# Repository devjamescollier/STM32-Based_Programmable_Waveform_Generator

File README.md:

# STM32-Based Programmable Waveform Generator

USB-powered programmable function generator built around an STM32C031K6T6 microcontroller and MCP4901 DAC. Generates clean sine, triangle, and square waveforms with amplitude control via potentiometer, mode selection via buttons, and visual feedback through status/signal LEDs.

Designed for lab and bench use with an SWD programming header, multiple test points, and robust power protection.

## Table of Contents
- [Schematic](#schematic)
- [Layout](#layout)
- [3D Model](#3d-model)
- [Overview](#overview)
- [Specifications](#specifications)
- [Results](#results)
- [Software](#software)
- [Tech Stack](#tech-stack)
- [Equipment](#equipment)
- [Manufacturing](#manufacturing)
- [Repository Structure](#repository-structure)
- [Contact](#contact)
- [License](#license)

## Schematic

## Layout

## 3D Model

## Overview

The board is a compact USB-powered waveform generator centred on an STM32C031K6T6 microcontroller.

| Section                         | Description                                                                                                            |
| ---                             | ---                                                                                                                    |
| **Digital Core**                | The STM32 generates waveform data and drives an MCP4901 8-bit SPI DAC.                                                 |
| **Analog Front-End**            | A TLV2372 dual op-amp and discrete MOSFET switching produce clean sine, triangle, and square outputs.                  |
| **User Interface**              | Three tactile switches provide waveform selection, mode/settings control, and reset. Five status/signal LEDs provide visual feedback, while a potentiometer controls amplitude. |
| **Power**                       | A USB Micro-B input supplies the board through an LM1117 3.3 V regulator with polyfuse protection.                     |

## Specifications

| Parameter                         | Value                                  |
| --------------------------------- | -------------------------------------- |
| **Microcontroller**               | STM32C031K6T6                          |
| **DAC**                           | MCP4901, 8-bit SPI                     |
| **Waveforms**                     | Sine, triangle, and square             |
| **Sine/Triangle Frequency Range** | 1 Hz–50 kHz                            |
| **Square-Wave Frequency Range**   | 1 Hz–100 kHz                           |
| **Amplitude**                     | 0–3.0 Vpp, controlled by potentiometer |
| **Output Impedance**              | ~50 Ω                                  |
| **Power Input**                   | 5 V USB                                |
| **Typical Current**               | 28 mA                                  |
| **Maximum Current**               | 45 mA                                  |
| **Regulation**                    | 3.3 V ± 1.5%                           |
| **Board size**                    | 52 mm × 48 mm                          |

## Results

PCB measurements from the hand-soldered prototype:

| Waveform     | Frequency | Amplitude | THD / Rise-Fall | Notes                           |
| -----------: | --------: | --------: | --------------: | ------------------------------: |
| **Sine**     | 1 kHz     | 2.98 Vpp  | 0.72% THD       | Clean across the full range     |
| **Triangle** | 1 kHz     | 2.95 Vpp  | —               | Linear slope confirmed          |
| **Square**   | 10 kHz    | 3.01 Vpp  | 12 ns / 14 ns   | Fast edges with minimal ringing |

Frequency response, amplitude accuracy (±1.2%), and load regulation were verified using an Agilent Technologies InfiniiVision MSO-X 3034A and Digilent Analog Discovery 3.

## Software

The firmware targets the STM32C031K6T6 and is written in C.

### Programming

1. Create a new STM32CubeIDE project targeting the STM32C031K6T6.
2. Replace the generated `Core/Src/main.c` with [`Software/main.c`](Software/main.c).
3. Configure the required GPIO, SPI, ADC, and timer peripherals.
4. Connect an ST-Link/V2 to the SWD header.
5. Build and flash the firmware through SWD.

## Tech Stack

| PCB Design | Firmware Development | Version Control | Repository Hosting | Circuit Simulation | IDE         | Language |
| :--------: | :------------------: | :-------------: | :----------------: | :----------------: | :---------: | :------: |
|  |  |  |  |  |  |  |

## Equipment

| Tool                   | Model                                          | Purpose |
| ---------------------- | ---------------------------------------------- | ------- |
| **Oscilloscope**       | Agilent Technologies InfiniiVision MSO-X 3034A | Waveform capture, THD, and rise/fall-time measurements |
| **Mixed-signal tool**  | Digilent Analog Discovery 3                    | Frequency-response and spectrum analysis               |
| **Multimeter**         | Tektronix DMM4020A                             | DC accuracy and current-draw measurements              |
| **Programmer**         | ST-Link/V2                                     | Firmware flashing and SWD debugging                    |
| **USB Power Analyzer** | —                                              | Input-current and efficiency verification              |
| **Soldering station**  | —                                              | Hand assembly of all SMD and through-hole components   |

## Manufacturing

Production files are provided in the [`Manufacturing`](Manufacturing/) directory:

| File | Purpose |
| ---- | ------- |
| [`JLCPCB/Waveform_Generator_Gerbers.zip`](Manufacturing/JLCPCB/Waveform_Generator_Gerbers.zip) | Gerber and drill archive, ready to upload to JLCPCB |
| [`JLCPCB/Waveform_Generator_JLCPCB_BOM.csv`](Manufacturing/JLCPCB/Waveform_Generator_JLCPCB_BOM.csv) | Bill of materials with LCSC part numbers (JLCPCB format) |
| [`JLCPCB/Waveform_Generator_JLCPCB_CPL.csv`](Manufacturing/JLCPCB/Waveform_Generator_JLCPCB_CPL.csv) | Component placement list (JLCPCB format) |
| [`Gerbers`](Manufacturing/Gerbers/) | Individual Gerber (copper, mask, silkscreen, paste, outline) and Excellon drill files |
| [`Assembly/STM32-Based_Programmable_Waveform_Generator-all-pos.csv`](Manufacturing/Assembly/STM32-Based_Programmable_Waveform_Generator-all-pos.csv) | KiCad component position file (generic pick-and-place) |

### Ordering from JLCPCB

1. Upload `Waveform_Generator_Gerbers.zip` (2-layer, 52 mm × 48 mm).
2. Enable PCB Assembly, then upload `Waveform_Generator_JLCPCB_BOM.csv` and `Waveform_Generator_JLCPCB_CPL.csv`.
3. Check component rotation and polarity in the JLCPCB placement preview, especially U1, U2, U4, U5, Q3, Q4, D1–D5, and the tantalum capacitors C7 and C8.

> **Note:** At the time of writing, U1 (STM32C031K6T6, LCSC C5456169) and J2 (Amphenol 10104110-0001LF, LCSC C2931352) are stocked by LCSC but not held in JLCPCB's assembly inventory. Pre-order them into your JLCPCB parts library before placing the assembly order. TP1–TP4 are bare test pads and are not assembled.

Verify all fabrication outputs against the KiCad design before ordering.

## Repository Structure

```text
STM32-Based_Programmable_Waveform_Generator
├── .gitignore                                                                  Git ignore rules for KiCad and OS temporary files
├── Docs                                                                        Documentation
│   └── Images                                                                  Board render, layout, and schematic images
│       ├── STM32-Based_Programmable_Waveform_Generator_3D_Model.png            3D render of the board
│       ├── STM32-Based_Programmable_Waveform_Generator_Schematic_Layout.png    PCB layout
│       ├── STM32-Based_Programmable_Waveform_Generator_Schematic.png           Schematic (PNG)
│       └── STM32-Based_Programmable_Waveform_Generator_Schematic.pdf           Schematic (PDF)
├── Hardware                                                                    Hardware design files
│   └── KiCad_Files                                                             KiCad project, schematic, PCB, and project libraries
│       ├── 3D_Models                                                           STEP models used in the 3D render
│       │   ├── LM1117IMP-3-3-NOPB.stp                                          LM1117IMP-3.3/NOPB linear voltage regulator
│       │   ├── TC33X-2-XXX.stp                                                 Bourns TC33X-2-103E potentiometer
│       │   └── USB-B-Micro.stp                                                 USB Micro-B receptacle
│       ├── Footprints                                                          Project footprint library
│       │   └── LM1117.pretty                                                   LM1117 footprints
│       │       ├── DCY0004A_L.kicad_mod
│       │       ├── DCY0004A_M.kicad_mod
│       │       └── DCY0004A_N.kicad_mod
│       ├── Symbols                                                             Project symbol library
│       │   └── LM1117
│       │       └── LM1117.kicad_sym                                            LM1117 linear voltage regulator symbol
│       ├── STM32-Based_Programmable_Waveform_Generator.kicad_pcb               KiCad PCB file
│       ├── STM32-Based_Programmable_Waveform_Generator.kicad_pro               KiCad project file
│       ├── STM32-Based_Programmable_Waveform_Generator.kicad_sch               KiCad schematic file
│       └── sym-lib-table                                                       Project symbol library table
├── Manufacturing                                                               Fabrication and assembly outputs
│   ├── Assembly                                                                Generic assembly data
│   │   └── STM32-Based_Programmable_Waveform_Generator-all-pos.csv             KiCad component position file
│   ├── Gerbers                                                                 Individual Gerber and drill files
│   │   ├── STM32-Based_Programmable_Waveform_Generator-B_Cu.gbl                Bottom copper
│   │   ├── STM32-Based_Programmable_Waveform_Generator-B_Mask.gbs              Bottom solder mask
│   │   ├── STM32-Based_Programmable_Waveform_Generator-B_Paste.gbp             Bottom paste
│   │   ├── STM32-Based_Programmable_Waveform_Generator-B_Silkscreen.gbo        Bottom silkscreen
│   │   ├── STM32-Based_Programmable_Waveform_Generator-Edge_Cuts.gm1           Board outline
│   │   ├── STM32-Based_Programmable_Waveform_Generator-F_Cu.gtl                Top copper
│   │   ├── STM32-Based_Programmable_Waveform_Generator-F_Mask.gts              Top solder mask
│   │   ├── STM32-Based_Programmable_Waveform_Generator-F_Paste.gtp             Top paste
│   │   ├── STM32-Based_Programmable_Waveform_Generator-F_Silkscreen.gto        Top silkscreen
│   │   ├── STM32-Based_Programmable_Waveform_Generator-NPTH.drl                Non-plated drill file
│   │   └── STM32-Based_Programmable_Waveform_Generator-PTH.drl                 Plated drill file
│   └── JLCPCB                                                                  Files ready to upload to JLCPCB
│       ├── Waveform_Generator_Gerbers.zip                                      Gerber and drill archive
│       ├── Waveform_Generator_JLCPCB_BOM.csv                                   Bill of materials with LCSC part numbers
│       └── Waveform_Generator_JLCPCB_CPL.csv                                   Component placement list
├── Software                                                                    Firmware
│   ├── LICENSE                                                                 MIT License for firmware
│   └── main.c                                                                  Firmware for the STM32C031K6T6
├── LICENSE                                                                     CERN Open Hardware Licence Version 2 – Permissive for hardware
└── README.md                                                                   Project README
```

## Contact
- GitHub: [@devjamescollier](https://github.com/devjamescollier)
- Email: [jwcollie@usc.edu](mailto:jwcollie@usc.edu)

## License

Copyright © 2026 James Collier

The hardware design files are licensed under the CERN Open Hardware
Licence Version 2 – Permissive. See [LICENSE](LICENSE).

The firmware is licensed under the MIT License. See
[Software/LICENSE](Software/LICENSE).

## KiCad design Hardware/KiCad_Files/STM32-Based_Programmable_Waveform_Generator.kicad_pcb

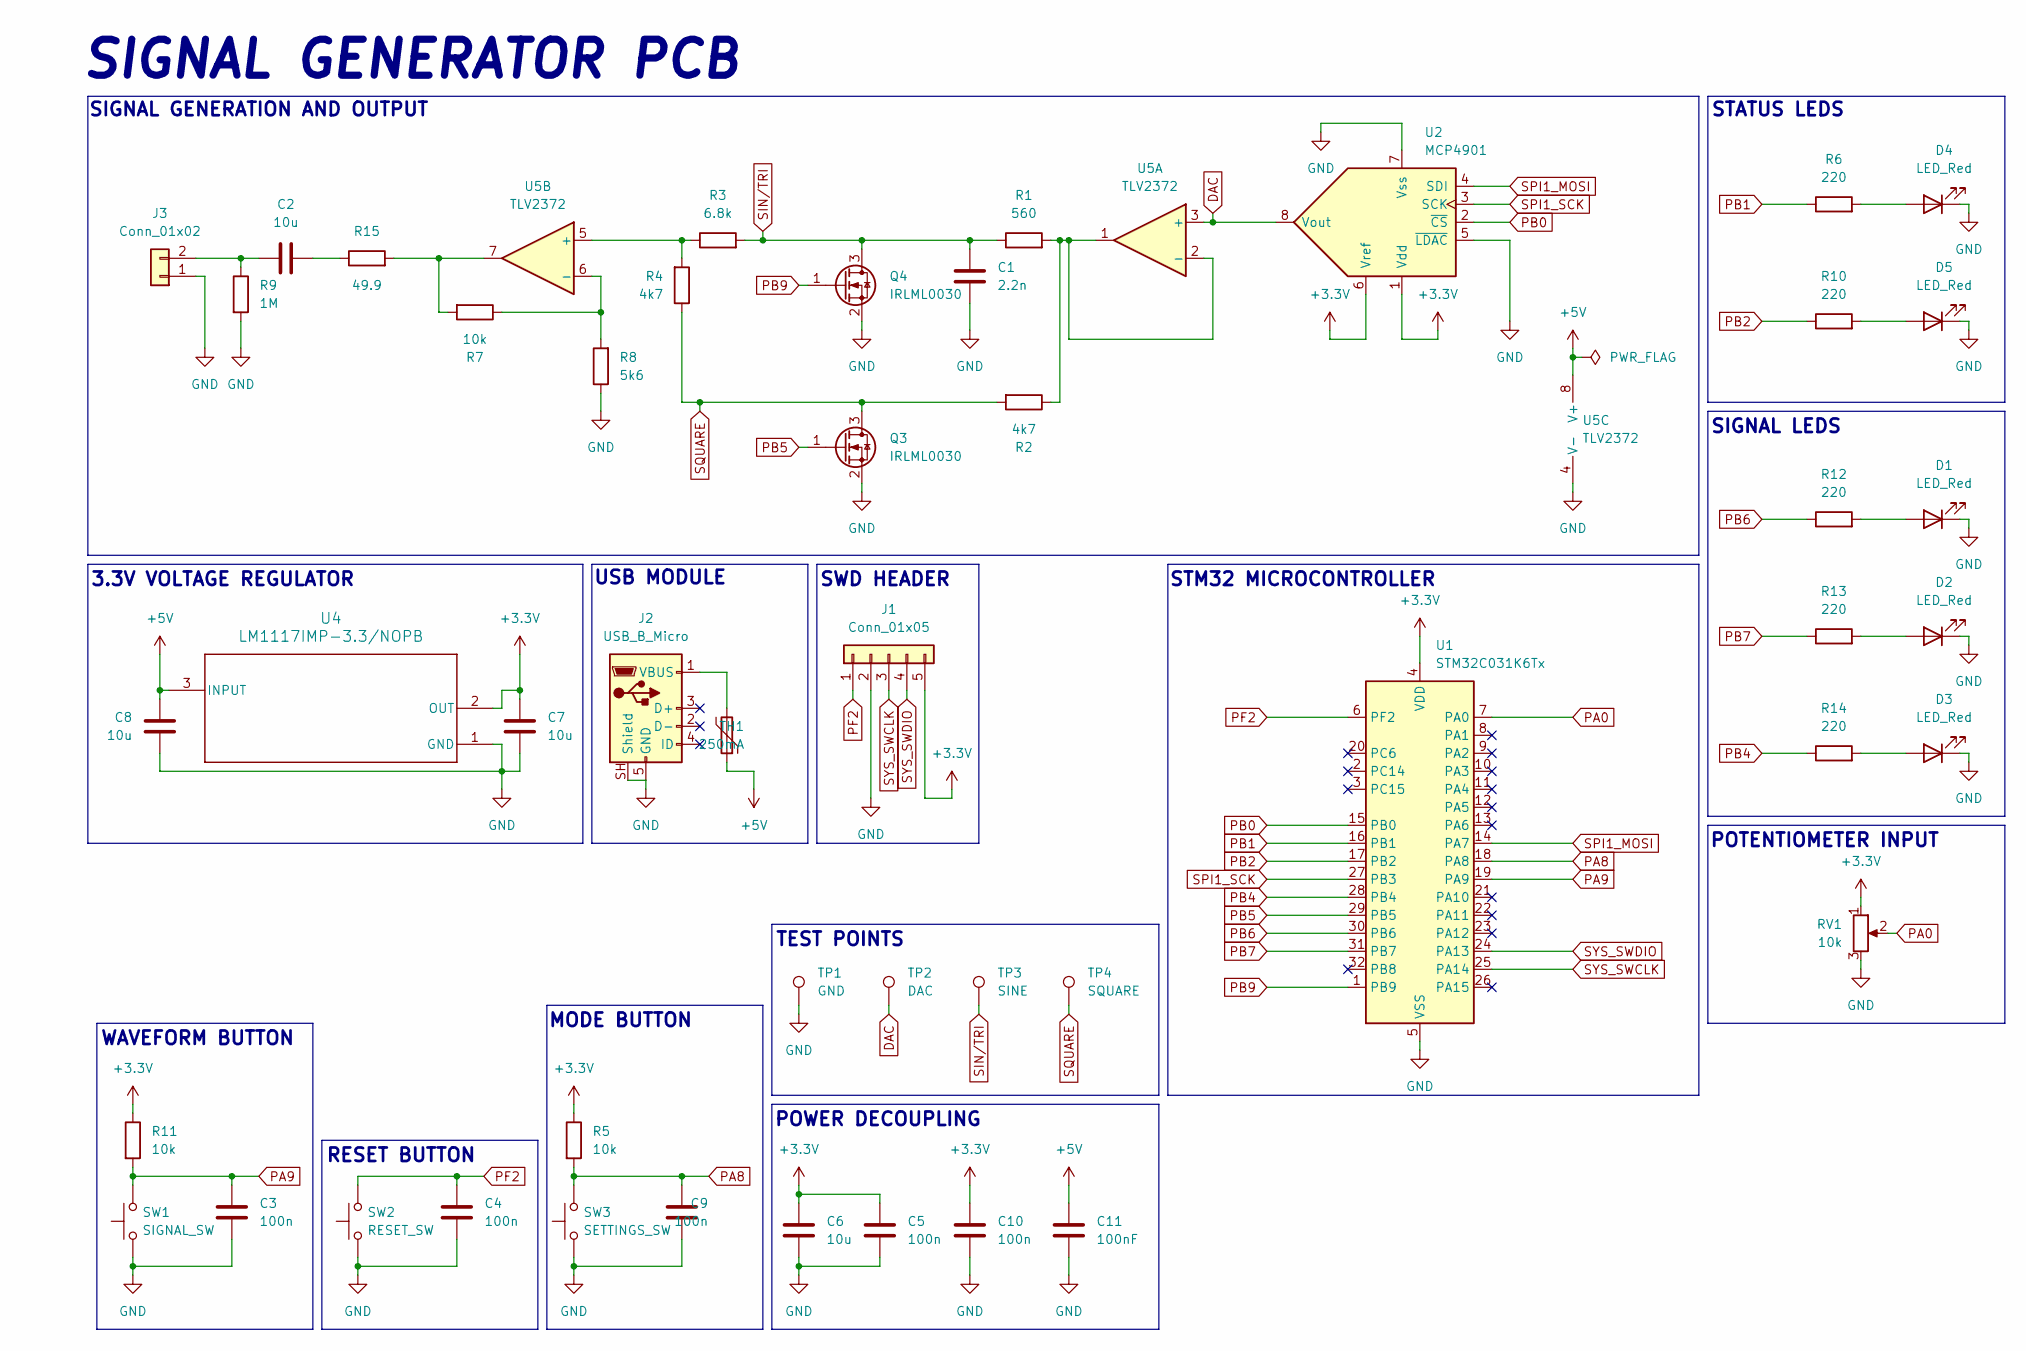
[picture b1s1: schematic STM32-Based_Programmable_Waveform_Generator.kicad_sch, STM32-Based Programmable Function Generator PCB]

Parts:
C1: 2.2n; C_0805_2012Metric
C2: 10u; C_1206_3216Metric
C3, C4, C5, C9, C10: 100n; C_0805_2012Metric
C6: 10u; C_0805_2012Metric
C7, C8: 10u; CP_EIA-3216-18_Kemet-A
C11: 100nF; C_0805_2012Metric
D1, D2, D3, D4, D5: LED_Red; LED_0805_2012Metric
J1: Conn_01x05; PinHeader_1x05_P2.54mm_Horizontal
J2: USB_B_Micro; USB_Micro-B_Amphenol_10104110_Horizontal
J3: Conn_01x02; JST_XH_B2B-XH-A_1x02_P2.50mm_Vertical
Q3, Q4: IRLML0030; SOT-23
R1: 560; R_0805_2012Metric
R2, R4: 4k7; R_0805_2012Metric
R3: 6.8k; R_0805_2012Metric
R5, R7, R11: 10k; R_0805_2012Metric
R6, R10, R12, R13, R14: 220; R_0805_2012Metric
R8: 5k6; R_0805_2012Metric
R9: 1M; R_0805_2012Metric
R15: 49.9; R_0805_2012Metric
RV1: 10k; Potentiometer_Bourns_TC33X_Vertical
SW1: SIGNAL_SW; SW_PUSH_6mm
SW2: RESET_SW; SW_PUSH_6mm
SW3: SETTINGS_SW; SW_PUSH_6mm
TH1: 250mA; Fuse_1206_3216Metric
TP1: GND; TestPoint_THTPad_D2.5mm_Drill1.2mm
TP2: DAC; TestPoint_THTPad_D2.5mm_Drill1.2mm
TP3: SINE; TestPoint_THTPad_D2.5mm_Drill1.2mm
TP4: SQUARE; TestPoint_THTPad_D2.5mm_Drill1.2mm
U1: STM32C031K6Tx; LQFP-32_7x7mm_P0.8mm
U2: MCP4901; SOIC-8_3.9x4.9mm_P1.27mm
U4: LM1117IMP-3.3/NOPB; SOT-223-3_TabPin2
U5: TLV2372; SOIC-8_3.9x4.9mm_P1.27mm

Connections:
+3.3V: C5.1, C6.1, C7.1, C10.1, J1.5, R5.1, R11.1, RV1.1, U1.4 (VDD), U2.1 (Vdd), U2.6 (Vref), U4.2 (OUT)
+5V: C8.1, C11.1, TH1.1, U4.3 (INPUT), U5.8 (V+)
DAC: TP2.1 (1_1), U2.8 (Vout), U5.3 (+)
GND: C1.2, C3.2, C4.2, C5.2, C6.2, C7.2, C8.2, C9.1, C10.2, C11.2, D1.1 (K), D2.1 (K), D3.1 (K), D4.1 (K), D5.1 (K), J1.2, J2.5 (GND), J2.SH (Shield), J3.1, Q3.2 (S), Q4.2 (S), R8.1, R9.2, RV1.3, SW1.1, SW2.1, SW3.1, TP1.1 (1_1), U1.5 (VSS), U2.5 (~LDAC), U2.7 (Vss), U4.1 (GND), U5.4 (V-)
unnamed: C2.2, R15.1
unnamed: D1.2 (A), R12.2
unnamed: D2.2 (A), R13.2
unnamed: D3.2 (A), R14.2
unnamed: D4.2 (A), R6.2
unnamed: D5.2 (A), R10.2
unnamed: J2.1 (VBUS), TH1.2
unnamed: C2.1, J3.2, R9.1
unnamed: R7.2, R15.2, U5.7
unnamed: R1.2, R2.1, U5.1, U5.2 (-)
unnamed: R3.1, R4.2, U5.5 (+)
unnamed: R7.1, R8.2, U5.6 (-)
PA0: RV1.2, U1.7 (PA0)
PA8: C9.2, R5.2, SW3.2, U1.18 (PA8)
PA9: C3.1, R11.2, SW1.2, U1.19 (PA9)
PB0: U1.15 (PB0), U2.2 (~CS)
PB1: R6.1, U1.16 (PB1)
PB2: R10.1, U1.17 (PB2)
PB4: R14.1, U1.28 (PB4)
PB5: Q3.1 (G), U1.29 (PB5)
PB6: R12.1, U1.30 (PB6)
PB7: R13.1, U1.31 (PB7)
PB9: Q4.1 (G), U1.1 (PB9)
PF2: C4.1, J1.1, SW2.2, U1.6 (PF2)
SIN/TRI: C1.1, Q4.3 (D), R1.1, R3.2, TP3.1 (1_1)
SPI1_MOSI: U1.14 (PA7), U2.4 (SDI)
SPI1_SCK: U1.27 (PB3), U2.3 (SCK)
SQUARE: Q3.3 (D), R2.2, R4.1, TP4.1 (1_1)
SYS_SWCLK: J1.3, U1.25 (PA14)
SYS_SWDIO: J1.4, U1.24 (PA13)

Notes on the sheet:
WAVEFORM BUTTON
POWER DECOUPLING
SIGNAL GENERATOR PCB
SWD HEADER
STATUS LEDS
SIGNAL LEDS
MODE BUTTON
RESET BUTTON
TEST POINTS
POTENTIOMETER INPUT
SIGNAL GENERATION AND OUTPUT
USB MODULE
STM32 MICROCONTROLLER
3.3V VOLTAGE REGULATOR

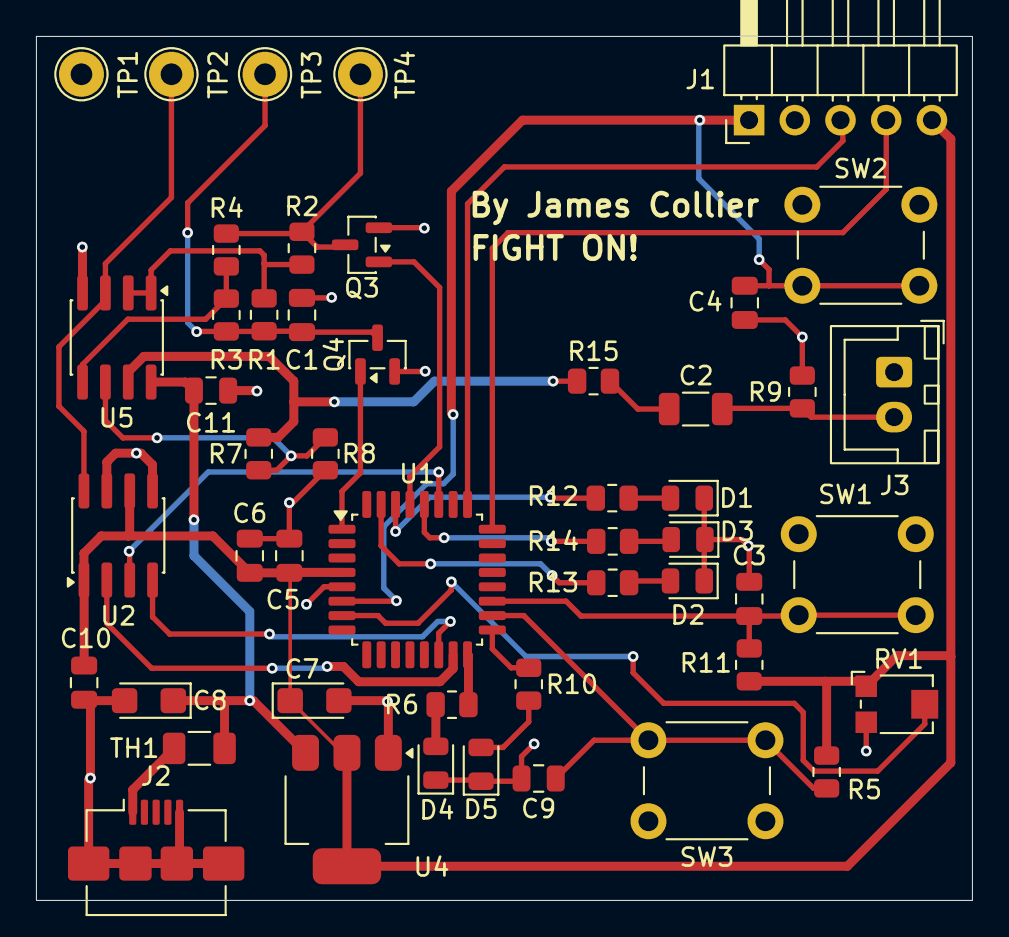
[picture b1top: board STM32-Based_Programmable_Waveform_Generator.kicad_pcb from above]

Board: 2 copper layers, 52.0 x 48.0 mm, 49 parts (0 on the bottom side), 34 nets.

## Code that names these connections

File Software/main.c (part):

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
static void OutputRouting_Update(void)
{
  const bool square = (waveform == WAVE_SQUARE);

  /* Q3/PB5 mutes the square path; Q4/PB9 mutes the sine/triangle path. */
  HAL_GPIO_WritePin(GPIOB, GPIO_PIN_5, square ? GPIO_PIN_RESET : GPIO_PIN_SET);
  HAL_GPIO_WritePin(GPIOB, GPIO_PIN_9, square ? GPIO_PIN_SET : GPIO_PIN_RESET);

  HAL_GPIO_WritePin(GPIOB, GPIO_PIN_6,
                    (waveform == WAVE_SINE) ? GPIO_PIN_SET : GPIO_PIN_RESET);
  HAL_GPIO_WritePin(GPIOB, GPIO_PIN_4,
                    (waveform == WAVE_TRIANGLE) ? GPIO_PIN_SET : GPIO_PIN_RESET);
  HAL_GPIO_WritePin(GPIOB, GPIO_PIN_7,
                    square ? GPIO_PIN_SET : GPIO_PIN_RESET);
}

static void ControlLeds_Update(void)
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  /*Configure GPIO pin Output Level */
  HAL_GPIO_WritePin(LD3_GPIO_Port, LD3_Pin, GPIO_PIN_RESET);

  /*Configure GPIO pins : PB9 PB0 PB1 PB2
                           PB4 PB5 PB6 PB7 */
  GPIO_InitStruct.Pin = GPIO_PIN_9|GPIO_PIN_0|GPIO_PIN_1|GPIO_PIN_2
                          |GPIO_PIN_4|GPIO_PIN_5|GPIO_PIN_6|GPIO_PIN_7;
  GPIO_InitStruct.Mode = GPIO_MODE_OUTPUT_PP;
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  GPIO_InitStruct.Pull = GPIO_NOPULL;
  HAL_GPIO_Init(T_NRST_GPIO_Port, &GPIO_InitStruct);

  /*Configure GPIO pins : PA8 PA9 */
  GPIO_InitStruct.Pin = GPIO_PIN_8|GPIO_PIN_9;
  GPIO_InitStruct.Mode = GPIO_MODE_IT_FALLING;
  GPIO_InitStruct.Pull = GPIO_PULLUP;
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
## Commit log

2026-05-26 Add project licenses
2026-05-27 Add KiCad symbols, footprints, and 3D models
2026-05-29 Add schematic and KiCad project file
2026-05-31 Add routed PCB layout
2026-06-02 Add waveform generation firmware
2026-06-03 Add Gerber and drill files
2026-06-04 Add pick-and-place file
2026-06-05 Add JLCPCB fabrication package
2026-06-06 Add schematic exports and board renders
2026-06-08 Add README

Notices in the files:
Software/main.c:
Copyright (c) 2023 STMicroelectronics.
All rights reserved.
This software is licensed under terms that can be found in the LICENSE file
README.md:
Hardware License: CERN-OHL-P-2.0
